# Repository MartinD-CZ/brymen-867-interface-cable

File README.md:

# Outdated - see the new revision [here](https://github.com/MartinD-CZ/brymen-867-869-interface-cable-rev20)!

# Brymen 867/869 adapter cable
*see the article [here](http://embedblog.eu/?p=475) or the listing [here](https://www.tindie.com/products/martind/brymen-867869-adapter-cable/)*

## Features
- reads data from Brymen 867/869(s) via infrared
- sends the measurements at 9600 baud via virtual serial port
- output data rate and format adjustable
- activity LED
- you **need **a 3D printed case to use this

*Here's how the finished adapter looks:*

*Here's how the serial output looks:*

*If you are ordering it without the USB cable (or want to reprogram it), here's the connection diagram:*

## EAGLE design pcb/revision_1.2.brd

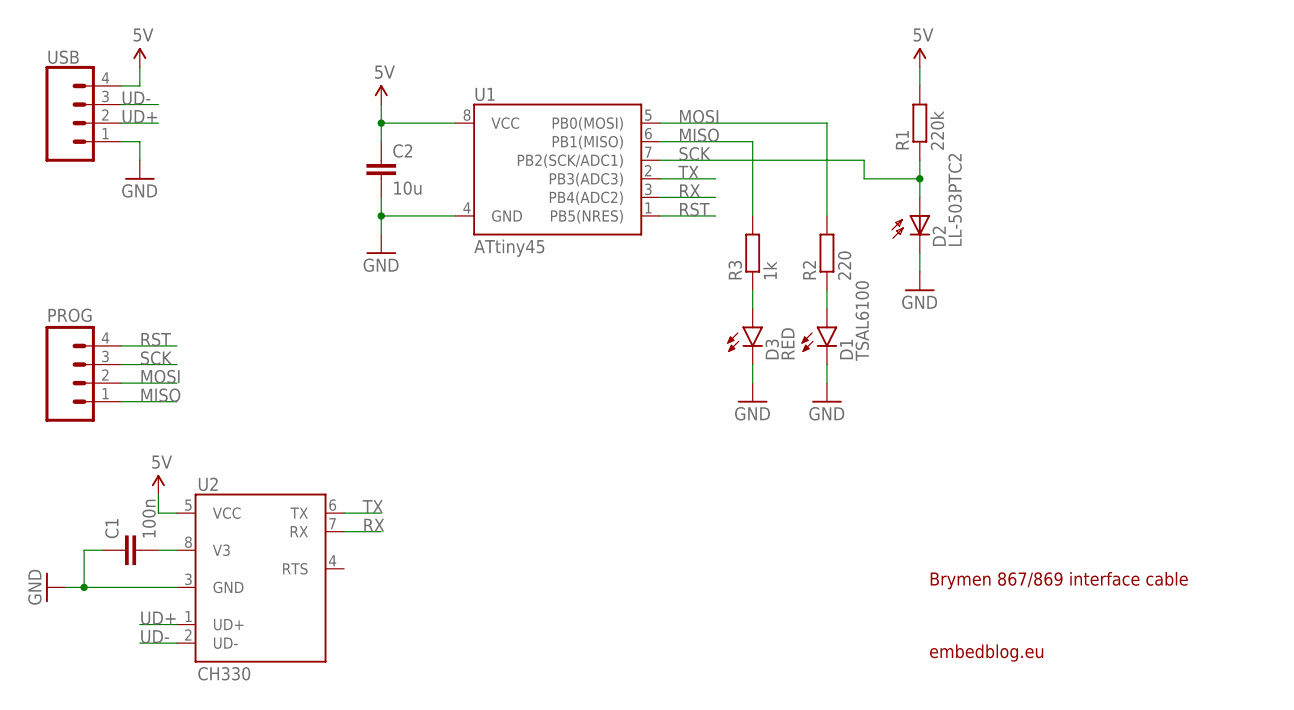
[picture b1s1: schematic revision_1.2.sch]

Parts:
C1: 100n; C0805
C2: 10u; C0805
D1: TSAL6100; LED5MM
D2: LL-503PTC2; BPX65
D3: RED; LED-1206
PROG: M04NO_SILK_ALL_ROUND; 1X04_NO_SILK_ALL_ROUND
R1: 220k; R0805
R2: 220; R0805
R3: 1k; R0805
U1: ATtiny45; SO08-EIAJ
U2: CH330; SO08
USB: CONN_04; 1X04

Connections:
5V: C2.1, R1.2, U1.8 (VCC), U2.5 (VCC), USB.4
GND: C1.1, C2.2, D1.K (C), D2.K (C), D3.C, U1.4 (GND), U2.3 (GND), USB.1
MISO: PROG.1, R3.2, U1.6 (PB1(MISO))
MOSI: PROG.2, R2.2, U1.5 (PB0(MOSI))
unnamed: C1.2, U2.8 (V3)
unnamed: D1.A, R2.1
unnamed: D3.A, R3.1
RST: PROG.4, U1.1 (PB5(NRES))
RX: U1.3 (PB4(ADC2)), U2.7 (RX)
SCK: D2.A, PROG.3, R1.1, U1.7 (PB2(SCK/ADC1))
TX: U1.2 (PB3(ADC3)), U2.6 (TX)
UD+: U2.1 (UD+), USB.2
UD-: U2.2 (UD-), USB.3

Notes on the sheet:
Brymen 867/869 interface cable
embedblog.eu

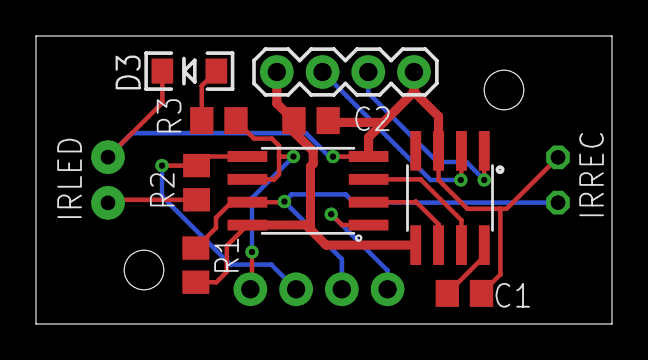
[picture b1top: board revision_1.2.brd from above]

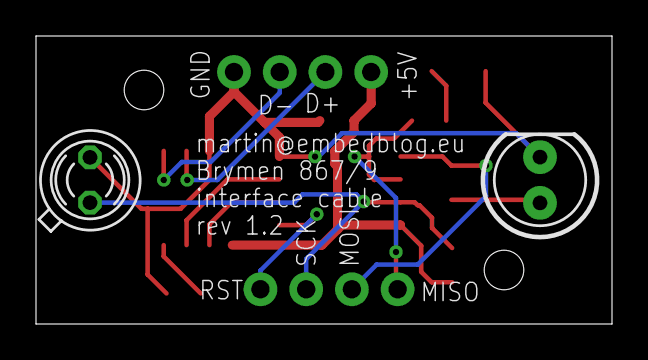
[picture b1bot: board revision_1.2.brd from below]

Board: 2 copper layers, 32.0 x 16.0 mm, 12 parts (2 on the bottom side), 13 nets.

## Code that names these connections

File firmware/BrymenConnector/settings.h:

/*
 * settings.h
 *
 * Header with all the important settings
 * Author : martin@embedblog.eu
 * 
 * DEFAULT PINOUT:
 *										  ________
 *									RST -|°       |- Vcc = +5 V
 *		phototransistor collector = PB3	-|        |- PB2 = software UART RX
 *					 IR LED anode = PB4 -|        |- PB1 = software UART TX
 *									GND	-|________|- PB0 = activity LED
 */ 


#ifndef SETTINGS_H_
#define SETTINGS_H_

#define F_CPU 8000000

//SETTINGS FOR SOFTWARE UART
#define SUART_DELAY	104
#define STX_HIGH	PORTB |= (1 << PORTB1)
#define STX_LOW		PORTB &=~(1 << PORTB1)
#define SRX_LOW		!(PINB & (1 << PINB2))

#define IRLED_HIGH	PORTB |= (1 << PORTB4)
#define IRLED_LOW	PORTB &=~(1 << PORTB4)
#define IRTRAN_LOW	!(PINB & (1 << PINB3))
#define CLOCK_DELAY	150

#define LED_HIGH	PORTB |= (1 << PORTB0)
#define LED_LOW		PORTB &=~(1 << PORTB0)

//modes
#define MODE_5X_PER_SEC		0
#define MODE_1X_PER_SEC		1
#define MODE_STOP			2
#define MODE_SEND			3


#endif /* SETTINGS_H_ */

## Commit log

2018-10-28 V 1.0
    initial commit
2019-10-14 revision 1.2
    major rework, see blog
2019-10-18 minor fixes
2020-09-04 added connection diagram
2021-04-28 added outdated notice

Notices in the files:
parts and their libraries:
SparkFun-LED: Licensing: Creative Commons ShareAlike 4.0 International - https://creativecommons.org/licenses/by-sa/4.0
